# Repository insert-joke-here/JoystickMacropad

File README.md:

# Joystick Macropad

This is a 2x3 macropad + a joystick. (created so i can play more pc games and also for the hackclub program half-life!)

It can be plugged straight into your computer (maybe with an adapter if you need it?) and used as a keyboard/joystick however you wish!

It uses an adafruit feather 328p (which is compatible with the arduino IDE , so you can in fact use an arduino with the same code, but you will have to edit the footprint), this was just a cheaper option. The joystick provides analog input to two analog pins on the board and a digital input for whether the joystick is pressed down. The keys use a row / column setup, with a digital GPIO pin used for each row and column, actually saving a (wow 1 whole) pin over wiring each key to a pin. The code to check a key works by setting a row to HIGH, then checking each column to see which pin is active.

schematic:

the routing (also the cover image bc my computer cant load it in 3d):

The case for this project is available [here](https://github.com/insert-joke-here/JoyMacropadCase).

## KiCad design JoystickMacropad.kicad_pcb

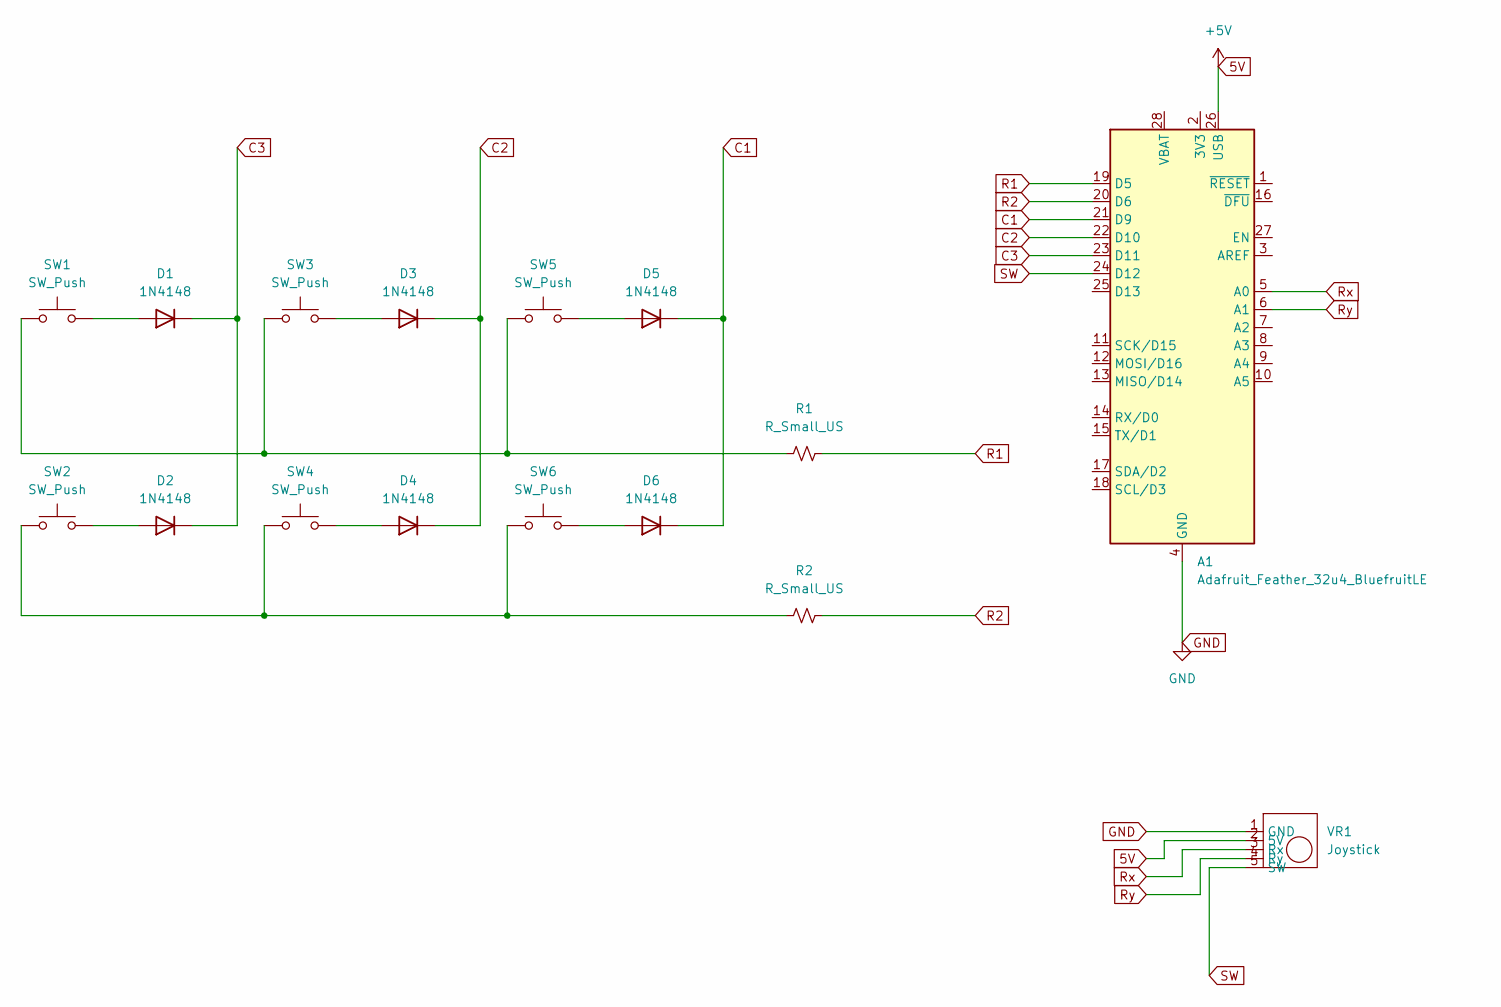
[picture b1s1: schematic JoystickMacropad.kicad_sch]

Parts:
A1: Adafruit_Feather_32u4_BluefruitLE; Adafruit_Feather
D1, D2, D3, D4, D5, D6: 1N4148; D_DO-35_SOD27_P7.62mm_Horizontal
R1, R2: R_Small_US; R_Axial_DIN0204_L3.6mm_D1.6mm_P5.08mm_Horizontal
SW1, SW2, SW3, SW4, SW5, SW6: SW_Push; SW_Cherry_MX_1.00u_PCB
VR1: Joystick; KY-023

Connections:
5V: A1.26 (USB), VR1.2 (5V)
C1: A1.21 (D9), D5.1 (K), D6.1 (K)
C2: A1.22 (D10), D3.1 (K), D4.1 (K)
C3: A1.23 (D11), D1.1 (K), D2.1 (K)
GND: A1.4 (GND), VR1.1 (GND)
unnamed: D1.2 (A), SW1.2
unnamed: D2.2 (A), SW2.2
unnamed: D3.2 (A), SW3.2
unnamed: D4.2 (A), SW4.2
unnamed: D5.2 (A), SW5.2
unnamed: D6.2 (A), SW6.2
unnamed: R1.1, SW1.1, SW3.1, SW5.1
unnamed: R2.1, SW2.1, SW4.1, SW6.1
R1: A1.19 (D5), R1.2
R2: A1.20 (D6), R2.2
Rx: A1.5 (A0), VR1.3 (Rx)
Ry: A1.6 (A1), VR1.4 (Ry)
SW: A1.24 (D12), VR1.5 (SW)

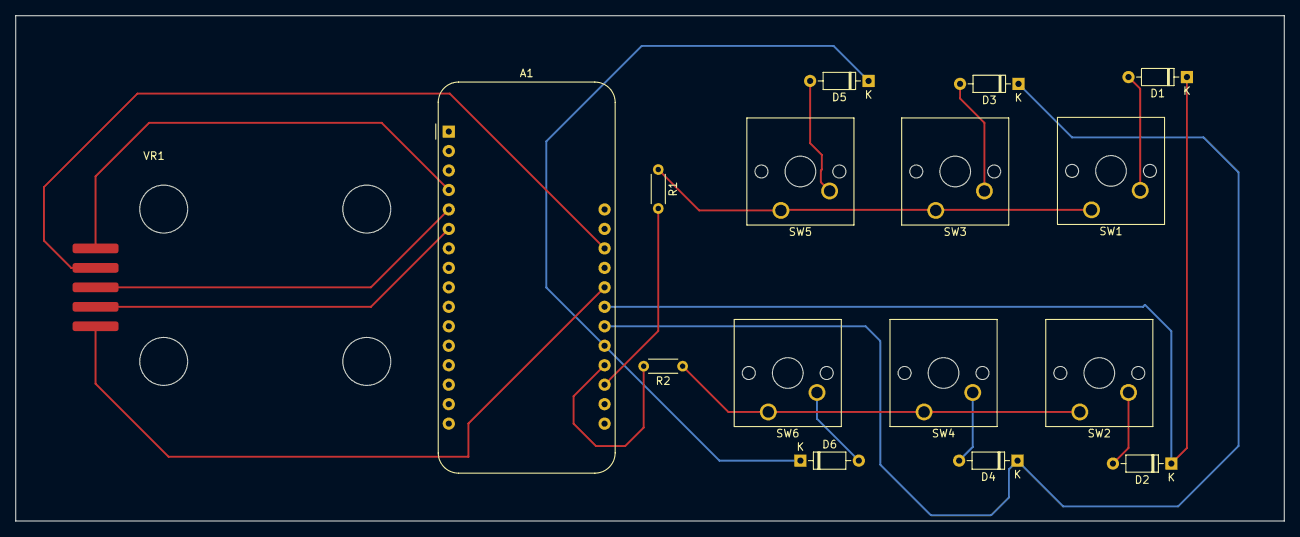
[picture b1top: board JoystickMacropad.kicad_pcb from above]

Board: 2 copper layers, 165.5 x 65.9 mm, 16 parts (0 on the bottom side), 18 nets.
